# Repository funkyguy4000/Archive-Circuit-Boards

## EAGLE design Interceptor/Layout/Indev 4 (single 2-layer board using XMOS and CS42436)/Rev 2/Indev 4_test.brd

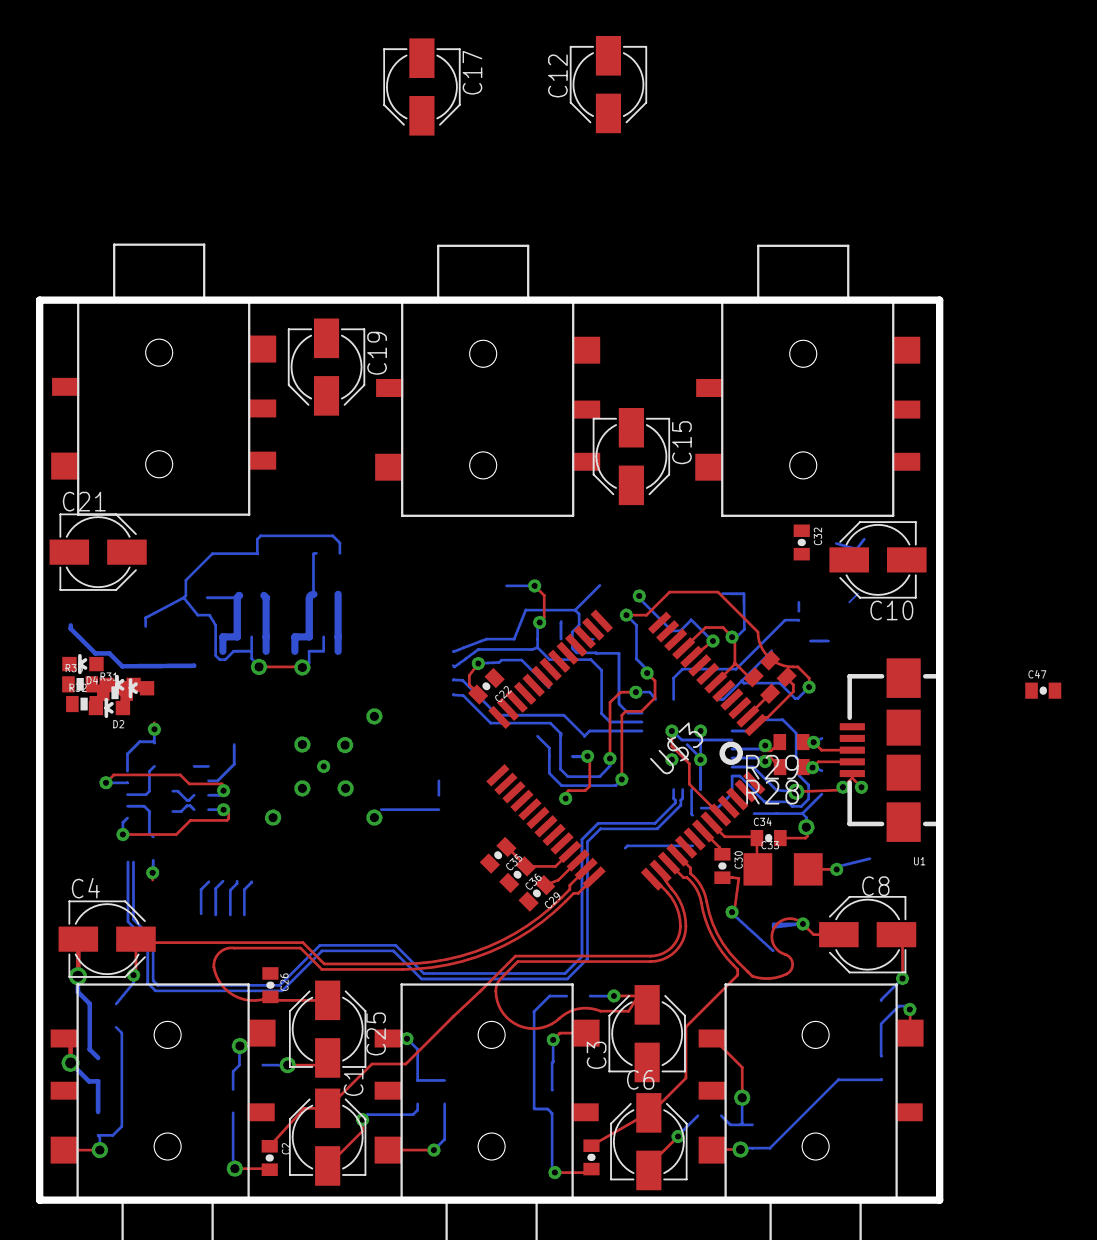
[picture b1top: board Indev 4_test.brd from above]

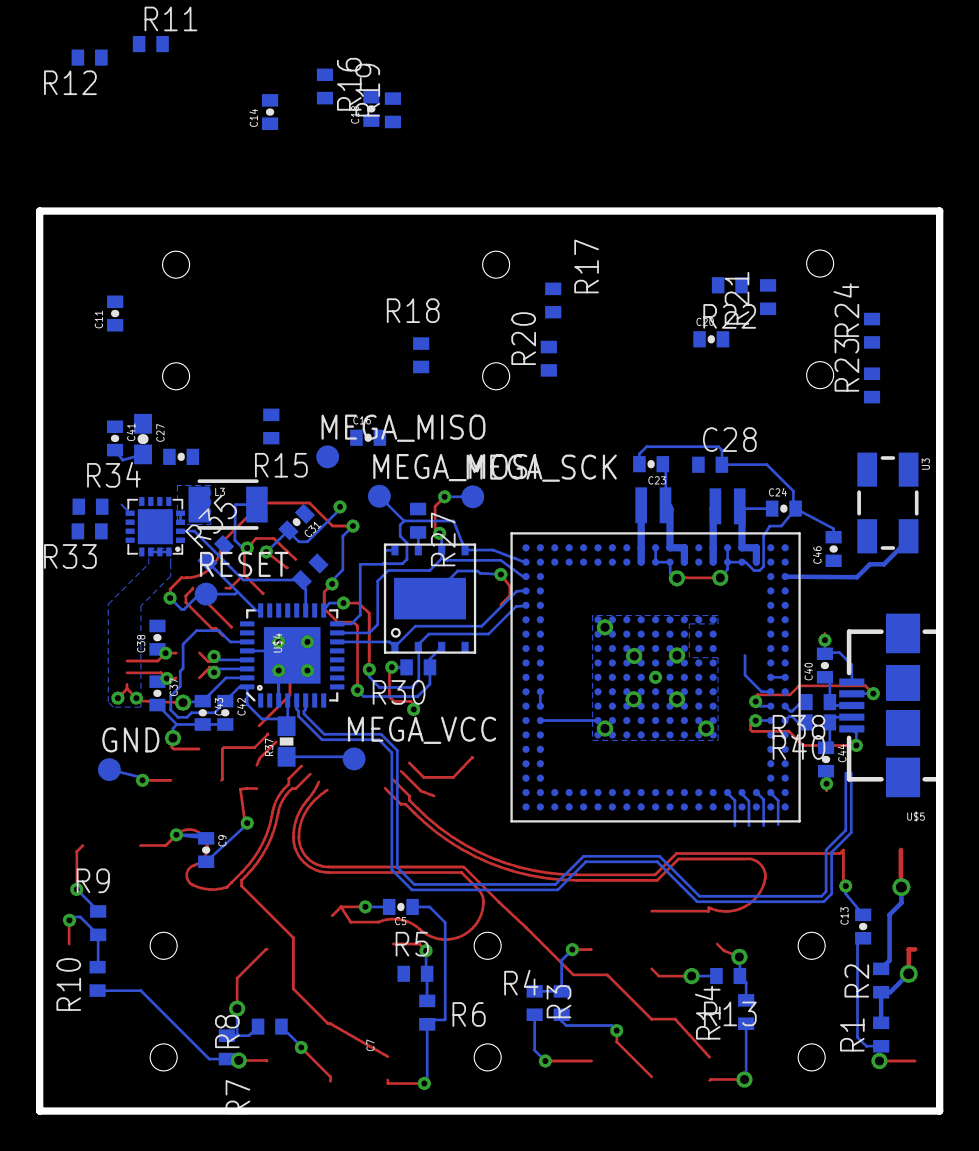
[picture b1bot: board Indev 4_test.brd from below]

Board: 2 copper layers, 50.0 x 50.0 mm, 113 parts (70 on the bottom side), 76 nets.

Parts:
C1, C3, C4, C6, C8, C10, C12, C15, C17, C19, C21, C25: 10u; PANASONIC_B
C2, C5, C7, C9, C11, C13, C14, C16, C18, C20, C22, C26, C39: 2700p; 0402-CAP
C23, C24, C29, C31, C43, C46, C47: 22uF; 0402-CAP
C27: 22u; 0603-CAP
C28: C0402
C30, C32: 100nF; 0402-CAP
C33: 100uF; 1206
C34, C35: .1uF; 0402-CAP
C36: 4.7uF; 0402-CAP
C37, C38, C40, C44: 100n; 0402-CAP
C41, C42: 1uF; 0402-CAP
D1: PWR OK; LED-0603
D2, D4: RED; LED-0603
D3: ALL OK; LED-0603
GND: TPB1,27; B1,27
J1, J2, J3, J4, J5, J6: SJ1-3514-SMT
L1, L2: 4.7uH; IND-2020
L3: 4.7uH; 1210
MEGA_MISO: TPB1,27; B1,27
MEGA_MOSI: TPB1,27; B1,27
MEGA_SCK: TPB1,27; B1,27
MEGA_VCC: TPB1,27; B1,27
R1, R3, R6, R7, R10, R11, R14, R16, R17, R20, R21, R24: 100k; R0402
R2, R4, R5, R8, R9, R12, R13, R15, R18, R19, R22, R23: 150; R0402
R25, R26: 4.7k; R0402
R27, R30, R35: 10K; R0402
R28, R29, R38, R40: 68; R0402
R31: 4.7k; 0402-RES
R32, R36: 68; 0402-RES
R33: 180k; R0402
R34: 40k; R0402
R37: 0; 0603-RES
R39: 10k; R0402
RESET: TPB1,27; B1,27
U1: USB-AB-MICRO-SMD
U3: OSCILLATOR5X3; CRYSTAL-SMD-5X3
U$1: LTC3601; QFN16-3X3
U$2: 25AA1024DFN; DFN8-5X6
U$3: CS42436; QFP-52
U$4: ATMEGA8U2; QFN-32
U$5: USB_AB; USB-AB-MICRO-SMD
U$6: XS1-U8A-124-FB217; 217-BGA(.8MM)

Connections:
3V3: C27.1, C28.1, C31.1, C32.1, C46.1, C47.1, L3.2, R25.1, R26.1, R27.1, R30.2, R31.2, R32.2, R33.2, R35.2, R36.2, R39.2, U3.1, U3.4, U$1.8, U$2.8, U$3.6, U$3.8, U$3.10, U$6.H18, U$6.I18, U$6.J1, U$6.J2, U$6.M1, U$6.R7, U$6.S1, U$6.S7
3V3_GOOD: R39.1, U$1.2, U$4.19
AIN1_N: C4.+, C13.1, U$3.38
AIN1_P: C25.+, C26.1, U$3.39
AIN2_N: C1.+, C2.1, U$3.40
AIN2_P: C3.+, C5.1, U$3.41
AIN3_N: C6.+, C7.1, U$3.42
AIN3_P: C8.+, C9.1, U$3.43
AOUT1_N: C10.+, C11.1, U$3.19
AOUT1_P: C12.+, C14.1, U$3.20
AOUT2_N: C15.+, C16.1, U$3.22
AOUT2_P: C17.+, C18.1, U$3.21
AOUT3_N: C19.+, C20.1, U$3.23
AOUT3_P: C21.+, C22.1, U$3.24
FB: R33.1, R34.2, U$1.11
FILT+: C33.1, C34.1, U$3.47
GND: C2.2, C5.2, C7.2, C9.2, C11.2, C13.2, C14.2, C16.2, C18.2, C20.2, C22.2, C23.2, C24.2, C26.2, C27.2, C28.2, C29.2, C30.2, C31.2, C32.2, C33.2, C34.2, C35.2, C36.2, C37.2, C38.2, C40.2, C41.2, C42.2, C43.2, C44.2, C46.2, C47.2, D1.C, D3.C, GND.TP, J1.1, J2.1, J3.1, J4.1, J5.1, J6.1, R1.2, R3.2, R6.2, R7.2, R10.2, R11.2, R14.2, R16.2, R17.2, R20.2, R21.2, R24.2, R34.1, U1.GND, U3.2, U$1.9, U$1.EXP, U$2.4, U$2.PAD, U$3.9, U$3.18, U$3.35, U$3.48, U$4.3, U$4.28, U$4.EP, U$5.GND, U$6.F6, U$6.F7, U$6.F8, U$6.F9, U$6.F10, U$6.F11, U$6.F12, U$6.F13, U$6.F14, U$6.G6, U$6.G7, U$6.G8, U$6.G9, U$6.G10, U$6.G11, U$6.G12, U$6.G13, U$6.G14, U$6.G18, U$6.H6, U$6.H7, U$6.H8, U$6.H9, U$6.H10, U$6.H11, U$6.H12, U$6.H13, U$6.H14, U$6.I6, U$6.I7, U$6.I8, U$6.I9, U$6.I10, U$6.I11, U$6.I12, U$6.I13, U$6.I14, U$6.J6, U$6.J7, U$6.J8, U$6.J9, U$6.J10, U$6.J11, U$6.J12, U$6.J13, U$6.J14, U$6.K6, U$6.K7, U$6.K8, U$6.K9, U$6.K10, U$6.K11, U$6.K12, U$6.K13, U$6.K14, U$6.L8, U$6.L9, U$6.L10, U$6.L11, U$6.L12, U$6.L13, U$6.L14, U$6.M8, U$6.M9, U$6.M10, U$6.M11, U$6.M12, U$6.M13, U$6.M14, U$6.N6, U$6.N7, U$6.N8, U$6.N9, U$6.N10, U$6.N11, U$6.N12, U$6.N13, U$6.N14, U$6.R4, U$6.R5, U$6.R9, U$6.R10, U$6.S5, U$6.S10
LED_N: D3.A, U$4.6
LED_P: D1.A, U$4.5
MEGA_VCC: C42.1, R37.2, U$4.4, U$4.27, U$4.32
unnamed: J1.2, R13.2, R14.1
unnamed: J1.3, R1.1, R2.2
unnamed: C4.-, R2.1
unnamed: D4.A, R36.1
unnamed: C25.-, R13.1
unnamed: MEGA_VCC.TP, R37.1
unnamed: U3.3, U$6.Q1
unnamed: J2.3, R3.1, R4.2
unnamed: C1.-, R4.1
unnamed: D2.A, R32.1
unnamed: J2.2, R5.2, R6.1
unnamed: C3.-, R5.1
unnamed: U$5.VBUS, U$6.G2
unnamed: J3.3, R7.1, R8.2
unnamed: C6.-, R8.1
unnamed: J3.2, R9.2, R10.1
unnamed: C8.-, R9.1
unnamed: C39.1, U$1.6
unnamed: U$5.ID, U$6.H2
unnamed: J4.3, R11.1, R12.2
unnamed: C10.-, R12.1
unnamed: C37.1, R28.1, U1.D-
unnamed: J4.2, R15.2, R16.1
unnamed: C12.-, R15.1
unnamed: J5.3, R17.1, R18.2
unnamed: C15.-, R18.1
unnamed: R25.2, U$3.1
unnamed: J5.2, R19.2, R20.1
unnamed: C17.-, R19.1
unnamed: R26.2, U$3.2
unnamed: J6.3, R21.1, R22.2
unnamed: C19.-, R22.1
unnamed: J6.2, R23.2, R24.1
unnamed: C21.-, R23.1
unnamed: C38.1, R29.1, U1.D+
unnamed: R27.2, U$2.7
PROG_USB_N: R28.2, U$4.30
PROG_USB_P: R29.2, U$4.29
RESET: D4.C, R30.1, R35.1, RESET.TP, U$2.3, U$4.24
ROM_CS: U$2.1, U$4.14, U$6.P19
ROM_MISO: MEGA_MISO.TP, U$2.2, U$4.17, U$6.O19
ROM_MOSI: MEGA_MOSI.TP, U$2.5, U$4.16, U$6.R19
ROM_SCK: MEGA_SCK.TP, U$2.6, U$4.15, U$6.Q19
SW: C39.2, L3.1, U$1.3, U$1.4
SW1: L1.P$2, U$6.R6, U$6.S6
SW2: L2.P$2, U$6.R11, U$6.S11
TRACK/SS: C41.1, U$1.1, U$1.7, U$1.10, U$1.12, U$1.13
USB2R_N: C44.1, R40.1, U$5.D-
USB2R_P: C40.1, R38.1, U$5.D+
USB2_N: R40.2, U$6.G1
USB2_P: R38.2, U$6.H1
USB_5V: C29.1, C30.1, C43.1, U1.VBUS, U$1.14, U$1.15, U$1.16, U$3.37, U$3.46, U$4.31
VDD1V8: C23.1, L2.P$1, U$6.R8, U$6.S8, U$6.S9
VDDCORE: C24.1, L1.P$1, U$6.R3, U$6.S3, U$6.S4
VQ: C35.1, C36.1, U$3.36
XMOS_RST: D2.C, R31.1, U$3.5, U$4.20, U$6.I2

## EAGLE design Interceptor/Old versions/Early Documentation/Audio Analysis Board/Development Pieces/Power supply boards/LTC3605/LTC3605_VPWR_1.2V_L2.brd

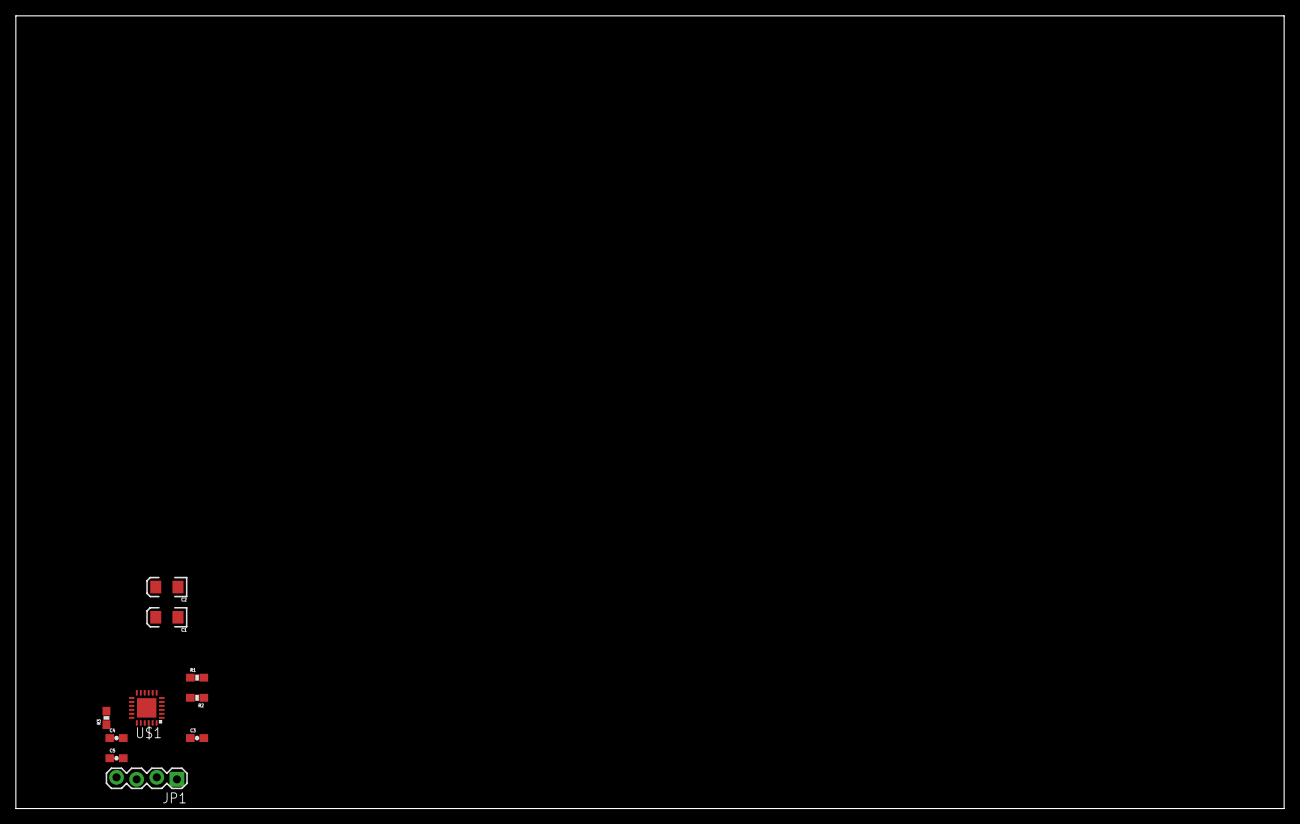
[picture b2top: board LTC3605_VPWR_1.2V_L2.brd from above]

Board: 2 copper layers, 160.0 x 100.0 mm, 10 parts (0 on the bottom side), 8 nets, no tracks yet.

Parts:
C1, C2: EIA3216
C3, C4, C5: 0603-CAP
JP1: 1X04_LOCK
R1, R2, R3: 0603-RES
U$1: LTC3605; QFN24

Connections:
GND: C1.C, C2.C, C4.1, C5.1, JP1.1, R2.1, U$1.10, U$1.22, U$1.EXP
unnamed: R1.1, R2.2, U$1.4
unnamed: C1.A, C2.A, C3.2, R1.2, U$1.9
unnamed: C3.1, U$1.20
unnamed: R3.1, U$1.19
unnamed: JP1.2, U$1.8
unnamed: JP1.3, U$1.7
unnamed: C4.2, C5.2, JP1.4, R3.2, U$1.17, U$1.18

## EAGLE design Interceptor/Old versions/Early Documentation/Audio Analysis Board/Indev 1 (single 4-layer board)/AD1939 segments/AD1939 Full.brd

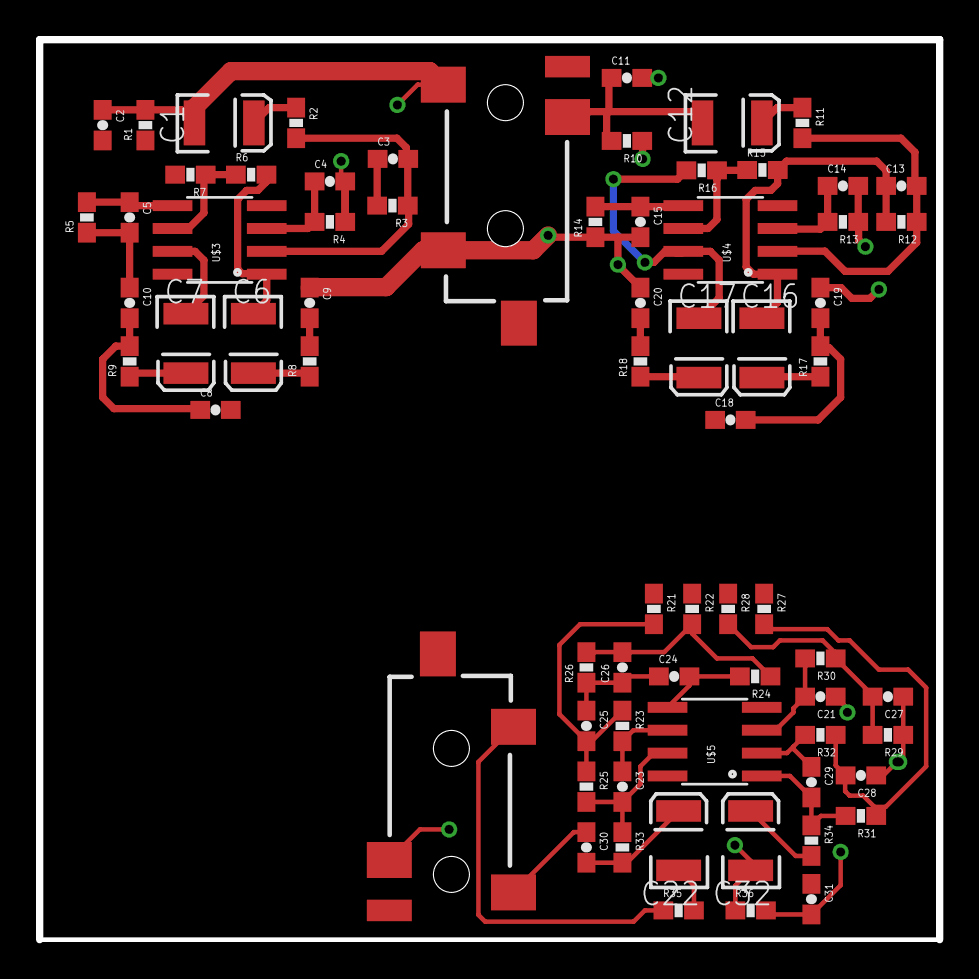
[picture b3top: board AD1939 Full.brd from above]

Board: 4 copper layers, 50.0 x 50.0 mm, 72 parts (1 on the bottom side), 46 nets.

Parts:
C1, C6, C7, C12, C16, C17, C22, C32: EIA3528
C2, C3, C4, C5, C8, C9, C10, C11, C13, C14, C15, C18, C19, C20, C21, C23, C24, C25, C26, C27, C28, C29, C30, C31: 0603-CAP
R1, R2, R3, R4, R5, R6, R7, R8, R9, R10, R11, R12, R13, R14, R15, R16, R17, R18, R21, R22, R23, R24, R25, R26, R27, R28, R29, R30, R31, R32, R33, R34, R35, R36: 0603-RES
U1, U2: AUDIO-JACK-3.5MM-SMD
U$2: AD1939; QFP64
U$3, U$4, U$5: OP275; SO-8

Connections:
ADC1LM: C8.1, C10.2, R9.2, U$2.54
ADC1LP: C8.2, C9.2, R8.2, U$2.53
ADC1RN: C18.1, C20.2, R18.2, U$2.56
ADC1RP: C18.2, C19.2, R17.2, U$2.55
GND: C1.C, C2.1, C2.2, C4.2, C5.2, C9.1, C10.1, C11.2, C14.2, C15.2, C19.1, C20.1, C21.1, C27.1, C28.1, C31.2, R1.1, R1.2, R4.1, R5.1, R10.1, R13.1, R14.1, R29.1, R36.2, U1.SLEEVE, U1.TIP
HP_RIGHT_INPUT: C11.1, C12.C, R10.2, U1.RING
LEFT_+IN_A: C4.1, R4.2, U$3.3
LEFT_+IN_B: C5.1, R5.2, U$3.5
LEFT_-IN_A: C3.2, R2.2, R3.1, U$3.2
LEFT_=IN_B: R6.1, R7.1, U$3.6
LEFT_OUT_A: C6.C, R6.2, U$3.1
LEFT_OUT_B: C7.C, R7.2, U$3.7
unnamed: C1.A, R2.1
unnamed: C25.2, R21.2, R23.1, R25.1
unnamed: C3.1, R3.2
unnamed: C26.2, R22.2, R24.1, R26.2
unnamed: C6.A, R8.1
unnamed: C7.A, R9.1
unnamed: C27.2, R28.2, R29.2, R30.1
unnamed: C28.2, R27.2, R31.1, R32.1
unnamed: C12.A, R11.1
unnamed: C16.A, R17.1
unnamed: C17.A, R18.1
unnamed: C22.A, C30.2, R33.2
unnamed: C22.C, R35.2
unnamed: C31.1, C32.A, R34.2
OL1N: R21.1, U$2.37
OL1P: R22.1, U$2.36
OL1P_FUNK: C24.1, C25.1, C26.1, R26.1
OR1N: R27.1, U$2.39
OR1P: R28.1, U$2.38
OUT_+IN_A: C21.2, R30.2, U$5.3
OUT_+IN_B: C24.2, R24.2, U$5.5
OUT_-IN)B: C23.1, R23.2, U$5.6
OUT_-IN_A: C29.1, R32.2, U$5.2
OUT_L: R35.1, U2.TIP
OUT_OUT_A: C29.2, R31.2, R34.1, U$5.1
OUT_OUT_B: C23.2, R25.2, R33.1, U$5.7
OUT_R: C32.C, R36.1, U2.RING
OUT_SLEEVE: C30.1, U2.SLEEVE
RIGHT_+IN_A: C14.1, R13.2, U$4.3
RIGHT_+IN_B: C15.1, R14.2, U$4.5
RIGHT_-IN_A: C13.2, R11.2, R12.1, U$4.2
RIGHT_OUT_A: C13.1, C16.C, R12.2, R15.2, U$4.1
RIGHT_OUT_B: C17.C, R16.2, U$4.7
RIHGT_-IN_A: R15.1, R16.1, U$4.6

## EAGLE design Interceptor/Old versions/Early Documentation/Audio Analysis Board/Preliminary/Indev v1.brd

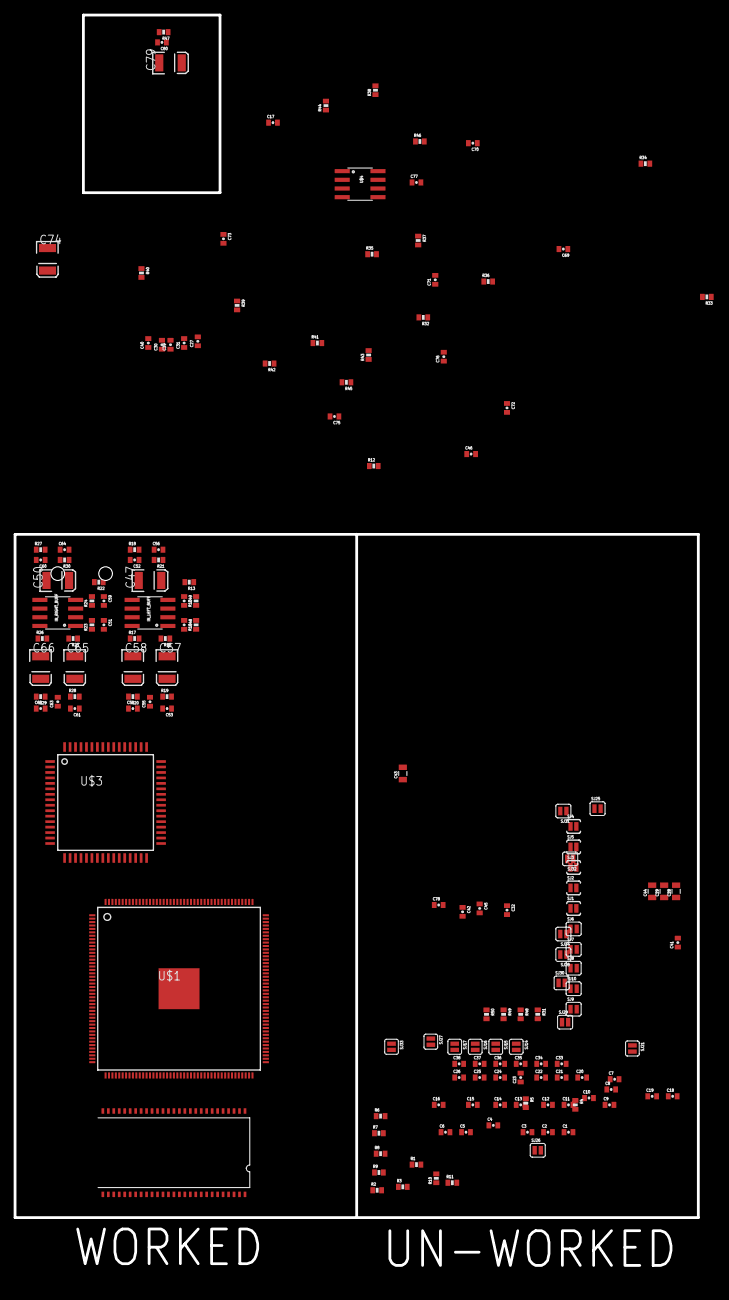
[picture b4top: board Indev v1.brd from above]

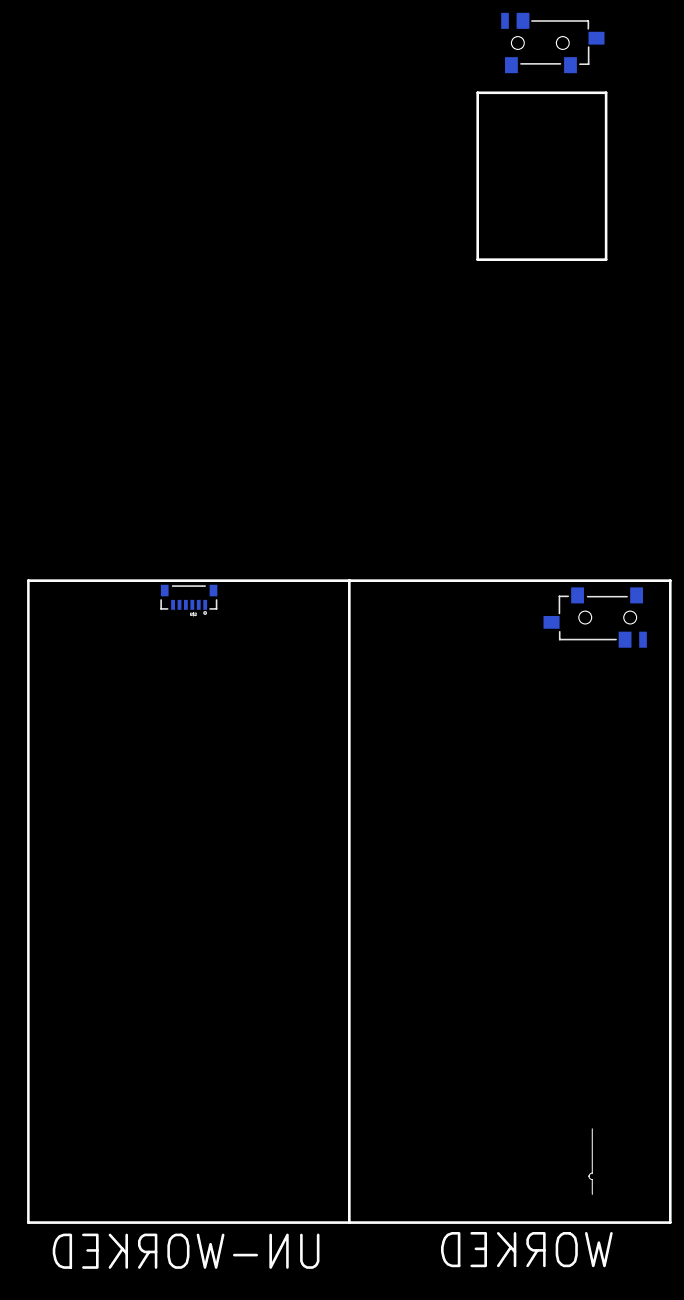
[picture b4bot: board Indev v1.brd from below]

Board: 2 copper layers, 100.0 x 176.0 mm, 162 parts (3 on the bottom side), 132 nets, no tracks yet.

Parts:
C1, C2, C3, C4, C5, C6, C7, C8, C9, C10, C11, C12, C13, C14, C15, C16, C17, C18, C19, C20, C21, C22, C23, C24, C25, C26, C27, C30, C31, C32, C33, C34, C35, C36, C37, C38, C39, C40, C41, C42, C45: .01uF; 0402-CAP
C28, C29, C43, C44: 10uF; 0805
C46, C48, C49, C51, C52, C53, C54, C55, C56, C59, C60, C61, C62, C63, C64, C69, C70, C71, C72, C73, C75, C76, C77, C78, C80: 0402-CAP
C47, C50, C57, C58, C65, C66, C74, C79: 47uF; EIA3528
INPUT_1: AUDIO-JACK-3.5MM-SMD
IN_LEFT_BUFF: OP275; SO-8
IN_RIGHT_BUFF: OP275; SO-8
OUTPUT1: AUDIO-JACK-3.5MM-SMD
R1, R2, R3, R4, R5, R12, R13, R14, R15, R16, R17, R18, R19, R20, R21, R22, R23, R24, R25, R26, R27, R28, R29, R30, R31, R32, R33, R34, R35, R36, R37, R38, R39, R40, R41, R42, R43, R44, R45, R46, R47, R48, R49, R50: 0402-RES
R6, R7, R8, R9, R10, R11: 33; 0402-RES
SJ1, SJ2, SJ3, SJ4, SJ5: SOLDERJUMPERNC2; SJ_2S-NOTRACE
SJ6, SJ7, SJ8, SJ9, SJ10, SJ14, SJ15, SJ16, SJ17, SJ21, SJ25, SJ26, SJ27, SJ28, SJ29, SJ30, SJ31, SJ32, SJ33, SJ34: SOLDERJUMPERNC; SJ_2S
U$1: ADSP-21483/6/7/9; LQFP-176
U$2: JTAG; JTAG-FPC
U$3: AD1939; QFP64
U$4: OP275; SO-8
U$7: MT48LC4M16A2; TSOP-54

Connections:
3.3V: R31.2, R50.2, SJ1.1, SJ2.1, SJ3.1, SJ4.1, SJ5.1, U$7.1, U$7.3, U$7.9, U$7.14, U$7.27, U$7.43, U$7.49
ABCLK: R6.2, R7.2, U$3.28
ABCLK_Z: R6.1, SJ27.2
AD1939_SOFT_RESET: SJ21.2, U$3.14
ADC1LN: C54.2, C55.1, R20.1, U$3.54
ADC1LP: C53.2, C55.2, R19.1, U$3.53
ADC1RN: C62.2, C63.1, R29.1, U$3.56
ADC1RP: C61.2, C63.2, R28.1, U$3.55
ALRCLK: R8.2, R9.2, U$3.29
ALRCLK_Z: R8.1, SJ28.2
ASDATA1: R10.2, U$3.27
ASDATA1_Z: R10.1, SJ25.2
ASDATA2: R11.2, U$3.26
ASDATA2_Z: R11.1, SJ26.2
DAI_P05: SJ25.1, U$1.87
DAI_P06: SJ26.1, U$1.86
DAI_P07: SJ27.1, U$1.73
DAI_P08: SJ28.1, U$1.94
DAI_P13: SJ33.1, U$1.74
DAI_P14: SJ34.1, U$1.95
DBCLK: R7.1, SJ33.2, U$3.21
DLRCLK: R9.1, SJ34.2, U$3.22
GND: C1.2, C2.2, C3.2, C4.2, C5.2, C6.2, C7.2, C8.2, C9.2, C10.2, C11.2, C12.2, C13.2, C14.2, C15.2, C16.2, C17.2, C18.2, C19.2, C20.2, C21.2, C22.2, C23.2, C24.2, C25.2, C26.2, C27.2, C28.2, C29.2, C30.2, C31.2, C32.2, C33.2, C34.2, C35.2, C36.2, C37.2, C38.2, C39.2, C40.2, C41.2, C42.2, C43.2, C44.2, C45.2, C49.1, C52.1, C53.1, C54.1, C56.1, C59.1, C60.1, C61.1, C62.1, C64.1, C75.1, C76.1, C78.1, C80.1, INPUT_1.SLEEVE, R1.1, R2.1, R3.1, R15.2, R18.2, R21.2, R24.2, R27.2, R30.2, R43.2, R47.1, R49.1, U$1.15, U$1.109, U$1.137, U$1.139, U$1.140, U$1.142, U$1.145, U$1.PAD, U$7.6, U$7.12, U$7.28, U$7.41, U$7.46, U$7.52, U$7.54
IN_3P5_LEFT: C47.C, C56.2, INPUT_1.TIP, R21.1
IN_3P5_RIGHT: C50.C, C64.2, INPUT_1.RING, R30.1
unnamed: R1.2, SJ1.2, U$1.7
unnamed: R2.2, SJ2.2, U$1.14
unnamed: R3.2, SJ3.2, U$1.106
unnamed: U$1.158, U$2.3
unnamed: U$1.151, U$2.4
unnamed: U$1.174, U$2.5
unnamed: R5.2, SJ4.2, U$1.22
unnamed: R4.1, R5.1
unnamed: R4.2, SJ5.2, U$1.5
unnamed: U$1.164, U$2.2
unnamed: SJ6.1, U$1.38
unnamed: SJ7.1, U$1.39
unnamed: SJ8.1, U$1.40
unnamed: SJ9.1, U$1.43
unnamed: SJ10.1, U$1.42
unnamed: SJ14.1, U$1.49
unnamed: SJ15.1, U$1.50
unnamed: SJ16.1, U$1.51
unnamed: SJ17.1, U$1.52
unnamed: SJ21.1, U$1.77
unnamed: SJ29.2, U$3.15
unnamed: SJ30.2, U$3.18
unnamed: SJ31.2, U$3.19
unnamed: SJ32.2, U$3.20
unnamed: SJ29.1, U$1.88
unnamed: SJ30.1, U$1.89
unnamed: SJ31.1, U$1.103
unnamed: SJ32.1, U$1.100
unnamed: C47.A, R13.2
unnamed: C48.1, IN_LEFT_BUFF.2, R13.1, R14.2
unnamed: C48.2, C57.C, IN_LEFT_BUFF.1, R14.1, R16.1
unnamed: C49.2, IN_LEFT_BUFF.3, R15.1
unnamed: IN_LEFT_BUFF.6, R16.2, R17.2
unnamed: C52.2, IN_LEFT_BUFF.5, R18.1
unnamed: C57.A, R19.2
unnamed: C58.A, R20.2
unnamed: C58.C, IN_LEFT_BUFF.7, R17.1
unnamed: C50.A, R22.2
unnamed: C51.1, IN_RIGHT_BUFF.2, R22.1, R23.2
unnamed: C51.2, C65.C, IN_RIGHT_BUFF.1, R23.1, R25.1
unnamed: C59.2, IN_RIGHT_BUFF.3, R24.1
unnamed: IN_RIGHT_BUFF.6, R25.2, R26.2
unnamed: C60.2, IN_RIGHT_BUFF.5, R27.1
unnamed: C66.C, IN_RIGHT_BUFF.7, R26.1
unnamed: C65.A, R28.2
unnamed: C66.A, R29.2
unnamed: C69.2, R33.1, R34.1, R36.2
unnamed: C69.1, C70.1, C72.1, R34.2
unnamed: C70.2, R32.1, R35.2, R37.2
unnamed: C71.2, R37.1, R39.2, U$4.7
unnamed: C71.1, R35.1, U$4.6
unnamed: C72.2, R36.1, U$4.5
unnamed: C73.2, C74.A, R39.1
unnamed: C74.C, OUTPUT1.TIP, R40.1
unnamed: C73.1, OUTPUT1.SLEEVE, R40.2
unnamed: C75.2, R42.1, R43.1, R45.2
unnamed: U$1.6, U$7.23
unnamed: C76.2, R41.1, R44.2, R46.2
unnamed: C77.1, R44.1, U$4.2
unnamed: C77.2, R38.2, R46.1, U$4.1
unnamed: C78.2, R45.1, U$4.3
unnamed: C79.A, C80.2, R38.1
unnamed: U$1.9, U$7.24
unnamed: C79.C, OUTPUT1.RING, R47.2
unnamed: U$1.10, U$7.25
unnamed: U$1.11, U$7.26
unnamed: U$1.12, U$7.29
unnamed: U$1.13, U$7.30
unnamed: U$1.16, U$7.31
unnamed: U$1.17, U$7.32
unnamed: U$1.20, U$7.33
unnamed: U$1.21, U$7.34
unnamed: U$1.27, U$7.22
unnamed: U$1.30, U$7.35
unnamed: U$1.32, U$7.20
unnamed: U$1.35, U$7.21
unnamed: R31.1, U$1.2, U$7.19
unnamed: U$1.3, U$7.37
unnamed: U$1.159, U$7.38
unnamed: U$1.172, U$7.18
unnamed: U$1.171, U$7.16
unnamed: U$1.175, U$7.17
unnamed: R48.1, U$1.1
unnamed: R48.2, R49.2, R50.1, U$7.15, U$7.39
unnamed: U$1.147, U$7.2
unnamed: U$1.148, U$7.4
unnamed: U$1.149, U$7.5
unnamed: U$1.150, U$7.7
unnamed: U$1.152, U$7.8
unnamed: U$1.154, U$7.10
unnamed: U$1.155, U$7.11
unnamed: U$1.157, U$7.13
unnamed: U$1.161, U$7.42
unnamed: U$1.162, U$7.44
unnamed: U$1.163, U$7.45
unnamed: U$1.165, U$7.47
unnamed: U$1.166, U$7.48
unnamed: U$1.168, U$7.50
unnamed: U$1.167, U$7.51
unnamed: U$1.170, U$7.53
OL1N: R32.2, U$3.37
OL1P: R33.2, U$3.36
OR1N: R41.2, U$3.39
OR1P: R42.2, U$3.38
VCCINT: C1.1, C2.1, C3.1, C4.1, C5.1, C6.1, C7.1, C8.1, C9.1, C10.1, C11.1, C12.1, C13.1, C14.1, C15.1, C16.1, C17.1, C18.1
VDDEXT: C30.1, C31.1, C32.1, C33.1, C34.1, C35.1, C36.1, C37.1, C38.1, C39.1, C40.1, C41.1, C42.1, C43.1, C44.1, C45.1, U$1.8, U$1.28, U$1.45, U$1.57, U$1.72, U$1.84, U$1.91, U$1.104, U$1.112, U$1.119, U$1.126, U$1.141, U$1.153, U$1.160
VDDINT: C19.1, C20.1, C21.1, C22.1, C23.1, C24.1, C25.1, C26.1, C27.1, C28.1, C29.1, U$1.4, U$1.23, U$1.29, U$1.34, U$1.37, U$1.41, U$1.48, U$1.62, U$1.65, U$1.68, U$1.78, U$1.85, U$1.90, U$1.93, U$1.102, U$1.105, U$1.107, U$1.113, U$1.114, U$1.116, U$1.123, U$1.129, U$1.133, U$1.143, U$1.156, U$1.169, U$1.176

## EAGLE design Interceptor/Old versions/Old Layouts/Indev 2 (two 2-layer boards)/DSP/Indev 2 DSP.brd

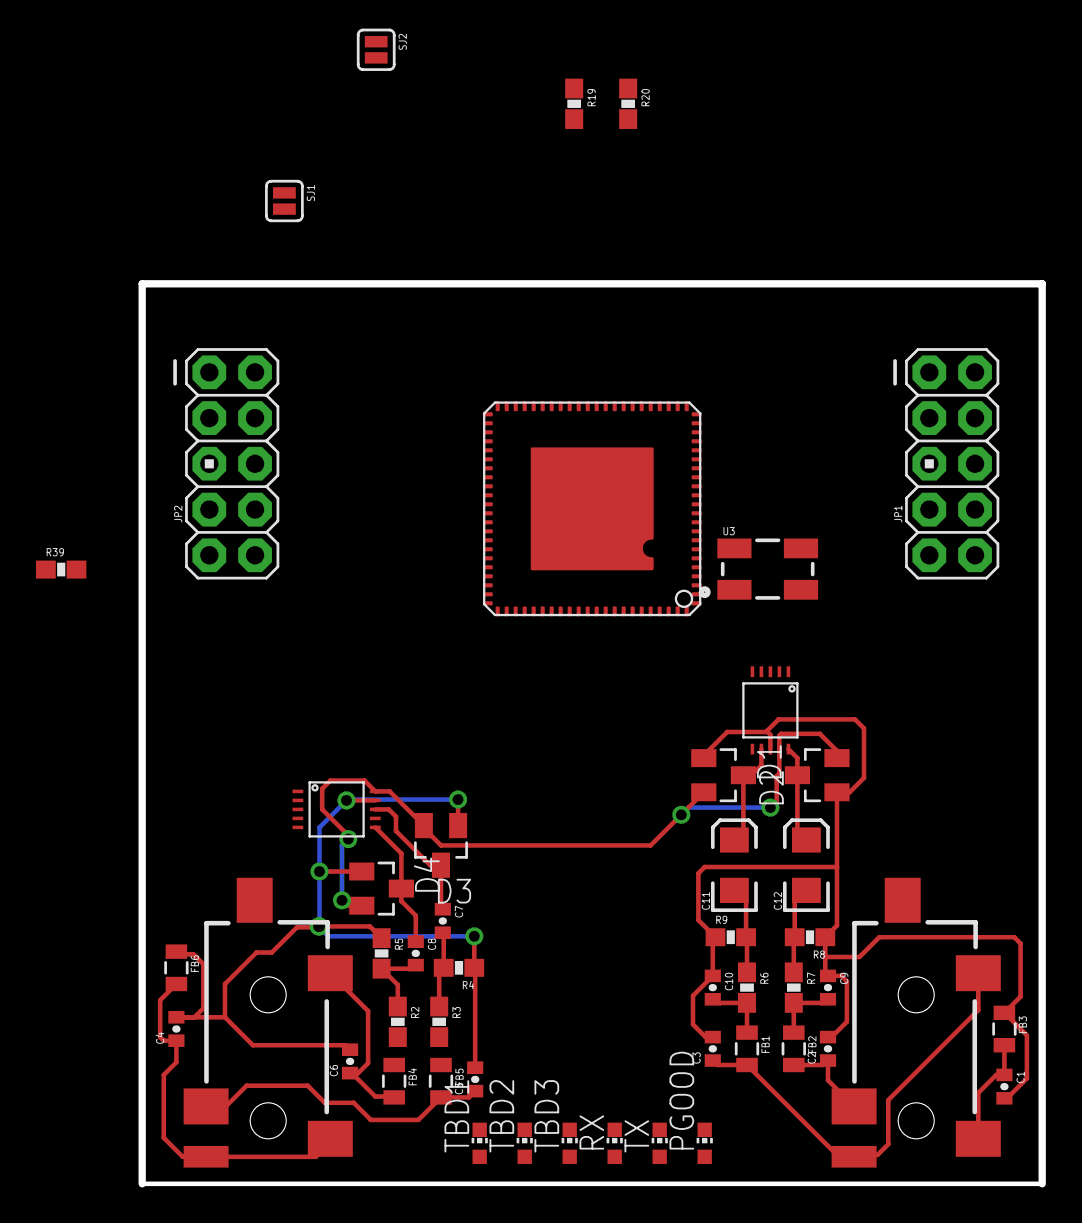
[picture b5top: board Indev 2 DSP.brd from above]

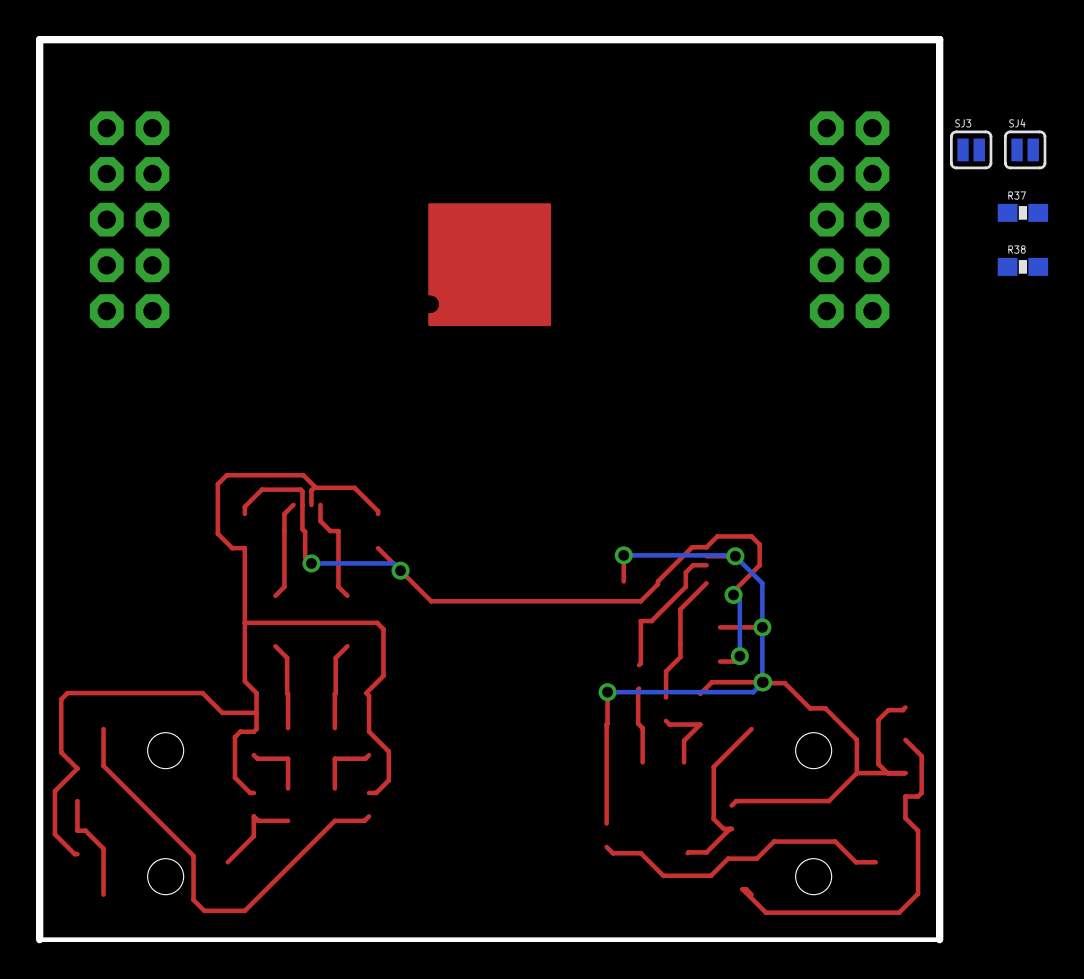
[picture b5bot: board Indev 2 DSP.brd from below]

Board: 2 copper layers, 50.0 x 50.0 mm, 53 parts (4 on the bottom side), 33 nets.

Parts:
C1, C2, C3, C4, C5, C6: 1000pF; 0402-CAP
C7, C8: 1uF; 0402-CAP
C9, C10: 2700pF; 0402-CAP
C11, C12: 3.3uF; EIA3216
D1, D2, D3, D4: BAT54S; SOT23
FB1, FB2, FB3, FB4, FB5, FB6: 220; 0805
JP1, JP2: M05X2PTH; AVR_ICSP
PGOOD: CHIP-LED0603
R2, R3: 6.81k; 0603-RES
R4, R5: 3.32k; 0603-RES
R6, R7: 470; 0603-RES
R8, R9, R19, R20, R37, R38, R39: 10k; 0603-RES
RX: CHIP-LED0603
SJ1, SJ2, SJ3, SJ4: SOLDERJUMPERNC; SJ_2S
TBD1, TBD2, TBD3: CHIP-LED0603
TX: CHIP-LED0603
U1, U2: AUDIO-JACK-3.5MM-SMD
U3: OSCILLATOR5X3-PIN1-INDICATED; CRYSTAL-OSC-SMD-5X3
U$1: ADSP-21479; QFN-88
U$2: CS4344-DAC; TSSOP-10
U$3: CS5343; TSSOP-10

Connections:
3.3V: R39.2, SJ1.1, SJ2.1, U3.1, U3.4
AINL: C6.1, FB4.2, U2.TIP
AINL_C: C8.1, D4.3, U$3.6
AINL_FB: FB4.1, R2.2
AINL_R: C8.2, R2.1, R5.2
AINR: C5.1, FB5.2, U2.RING
AINR_C: C7.1, D3.3, U$3.8
AINR_FB: FB5.1, R3.2
AINR_R: C7.2, R3.1, R4.2
AIN_SLEEV: C4.1, FB6.2, U2.SLEEVE
AOUTL: C3.1, FB1.2, U1.TIP
AOUTL_C: C11.A, D1.3, U$2.7
AOUTL_FB: C10.2, FB1.1, R6.2
AOUTL_R: C11.C, R6.1, R9.2
AOUTR: C2.1, FB2.2, U1.RING
AOUTR_C: C12.A, D2.3, U$2.10
AOUTR_FB: C9.2, FB2.1, R7.2
AOUTR_R: C12.C, R7.1, R8.2
AOUTS: C1.1, FB3.2, U1.SLEEVE
GND: C1.2, C2.2, C3.2, C4.2, C5.2, C6.2, C9.1, C10.1, D1.1, D2.1, D3.1, D4.1, FB3.1, FB6.1, R4.1, R5.1, R8.1, R9.1, R19.1, R20.1, R37.1, R38.1, U3.2, U$1.6, U$1.60, U$1.73, U$1.74, U$1.76, U$1.PAD, U$2.8, U$3.9
unnamed: U3.3, U$1.9
unnamed: SJ3.2, U$1.7
unnamed: SJ4.2, U$1.1
unnamed: R37.2, SJ4.1
unnamed: R38.2, SJ3.1
unnamed: R20.2, SJ1.2, U$1.2
unnamed: R39.1, U$1.14
unnamed: R19.2, SJ2.2, U$1.5
UART_CTS: JP1.8, U$1.29
UART_RTS: JP1.6, U$1.28
UART_RX: JP1.4, U$1.27
UART_TX: JP1.2, U$1.26
VCC: D1.2, D2.2, D3.2, D4.2, U$2.9, U$3.10

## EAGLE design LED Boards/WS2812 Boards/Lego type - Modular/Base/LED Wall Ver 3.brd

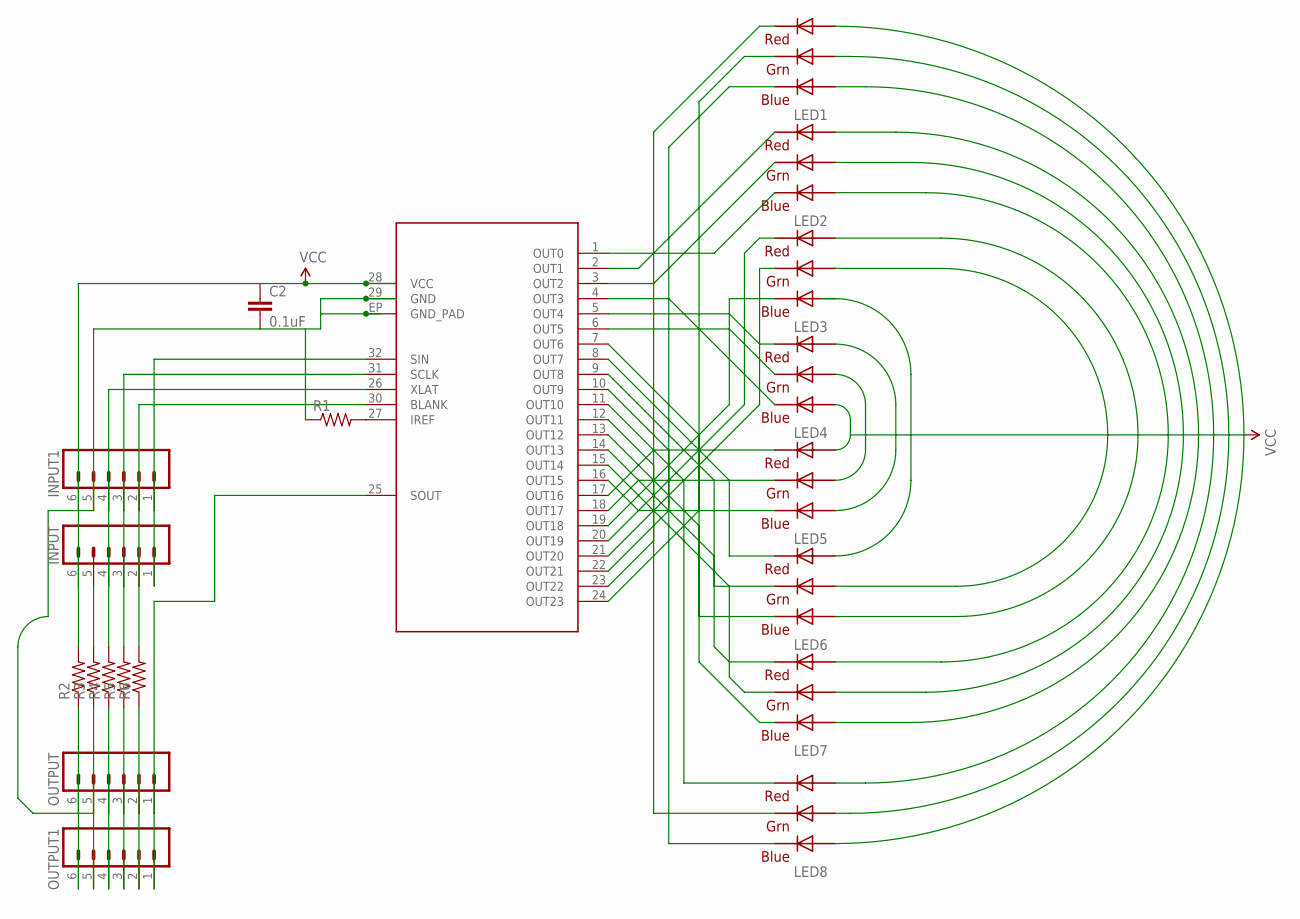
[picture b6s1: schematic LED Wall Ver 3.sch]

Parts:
C2: 0.1uF; 0402-CAP
INPUT, INPUT1: M06SMD-FEMALE-V2; 1X06-SMD-FEMALE-V2
LED1, LED2, LED3, LED4, LED5, LED6, LED7, LED8: RGBLED5050
OUTPUT, OUTPUT1: M06SMD; 1X06-SMD
R1: RESISTOR0603-RES; 0603-RES
R2, R3, R4, R5, R6: R-US_R1206W; R1206W
U$2: TLC5947; QFN-32

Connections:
BLANK: INPUT.2, INPUT1.2, R6.2, U$2.30 (BLANK)
BLANK_2: OUTPUT.2, OUTPUT1.2, R6.1
GND: C2.2, INPUT1.5, OUTPUT.5, OUTPUT1.5, R1.1, R3.1, U$2.29 (GND), U$2.EP (GND_PAD)
unnamed: LED2.4 (BLUE_C), U$2.1 (OUT0)
unnamed: LED2.5 (RED_C), U$2.2 (OUT1)
unnamed: LED2.6 (GREEN_C), U$2.3 (OUT2)
unnamed: LED8.4 (BLUE_C), U$2.10 (OUT9)
unnamed: LED4.5 (RED_C), U$2.5 (OUT4)
unnamed: LED4.4 (BLUE_C), U$2.4 (OUT3)
unnamed: LED4.6 (GREEN_C), U$2.6 (OUT5)
unnamed: LED6.4 (BLUE_C), U$2.7 (OUT6)
unnamed: LED6.5 (RED_C), U$2.8 (OUT7)
unnamed: LED6.6 (GREEN_C), U$2.9 (OUT8)
unnamed: LED8.5 (RED_C), U$2.11 (OUT10)
unnamed: LED8.6 (GREEN_C), U$2.12 (OUT11)
unnamed: LED7.4 (BLUE_C), U$2.13 (OUT12)
unnamed: LED7.5 (RED_C), U$2.14 (OUT13)
unnamed: LED7.6 (GREEN_C), U$2.15 (OUT14)
unnamed: LED5.4 (BLUE_C), U$2.16 (OUT15)
unnamed: LED5.5 (RED_C), U$2.17 (OUT16)
unnamed: LED5.6 (GREEN_C), U$2.18 (OUT17)
unnamed: LED3.4 (BLUE_C), U$2.19 (OUT18)
unnamed: R1.2, U$2.27 (IREF)
unnamed: LED3.5 (RED_C), U$2.20 (OUT19)
unnamed: LED3.6 (GREEN_C), U$2.21 (OUT20)
unnamed: LED1.4 (BLUE_C), U$2.22 (OUT21)
unnamed: LED1.5 (RED_C), U$2.23 (OUT22)
unnamed: LED1.6 (GREEN_C), U$2.24 (OUT23)
unnamed: INPUT.5, R3.2
SCLK: INPUT.3, INPUT1.3, R5.2, U$2.31 (SCLK)
SCLK_2: OUTPUT.3, OUTPUT1.3, R5.1
SIN: INPUT.1, INPUT1.1, U$2.32 (SIN)
SOUT: OUTPUT.1, OUTPUT1.1, U$2.25 (SOUT)
VCC: C2.1, INPUT.6, INPUT1.6, LED1.1 (GREEN_A), LED1.2 (RED_A), LED1.3 (BLUE_A), LED2.1 (GREEN_A), LED2.2 (RED_A), LED2.3 (BLUE_A), LED3.1 (GREEN_A), LED3.2 (RED_A), LED3.3 (BLUE_A), LED4.1 (GREEN_A), LED4.2 (RED_A), LED4.3 (BLUE_A), LED5.1 (GREEN_A), LED5.2 (RED_A), LED5.3 (BLUE_A), LED6.1 (GREEN_A), LED6.2 (RED_A), LED6.3 (BLUE_A), LED7.1 (GREEN_A), LED7.2 (RED_A), LED7.3 (BLUE_A), LED8.1 (GREEN_A), LED8.2 (RED_A), LED8.3 (BLUE_A), R2.2, U$2.28 (VCC)
VCC_2: OUTPUT.6, OUTPUT1.6, R2.1
XLAT: INPUT.4, INPUT1.4, R4.2, U$2.26 (XLAT)
XLAT_2: OUTPUT.4, OUTPUT1.4, R4.1

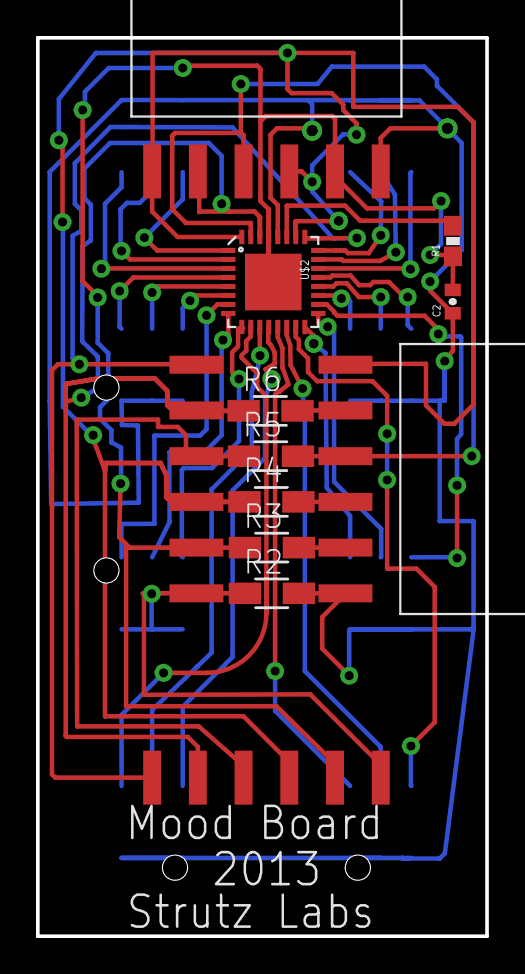
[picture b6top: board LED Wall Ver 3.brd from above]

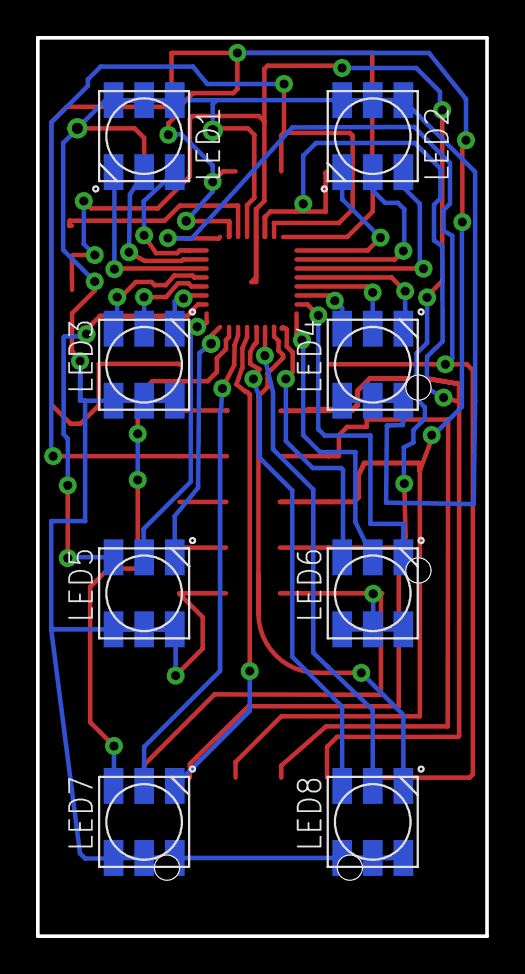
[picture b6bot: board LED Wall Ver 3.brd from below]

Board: 2 copper layers, 25.0 x 49.9 mm, 20 parts (8 on the bottom side), 37 nets.

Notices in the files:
parts and their libraries:
SparkFun-Connectors: Licensing: CC v3.0 Share-Alike You are welcome to use this library for commercial purposes.
